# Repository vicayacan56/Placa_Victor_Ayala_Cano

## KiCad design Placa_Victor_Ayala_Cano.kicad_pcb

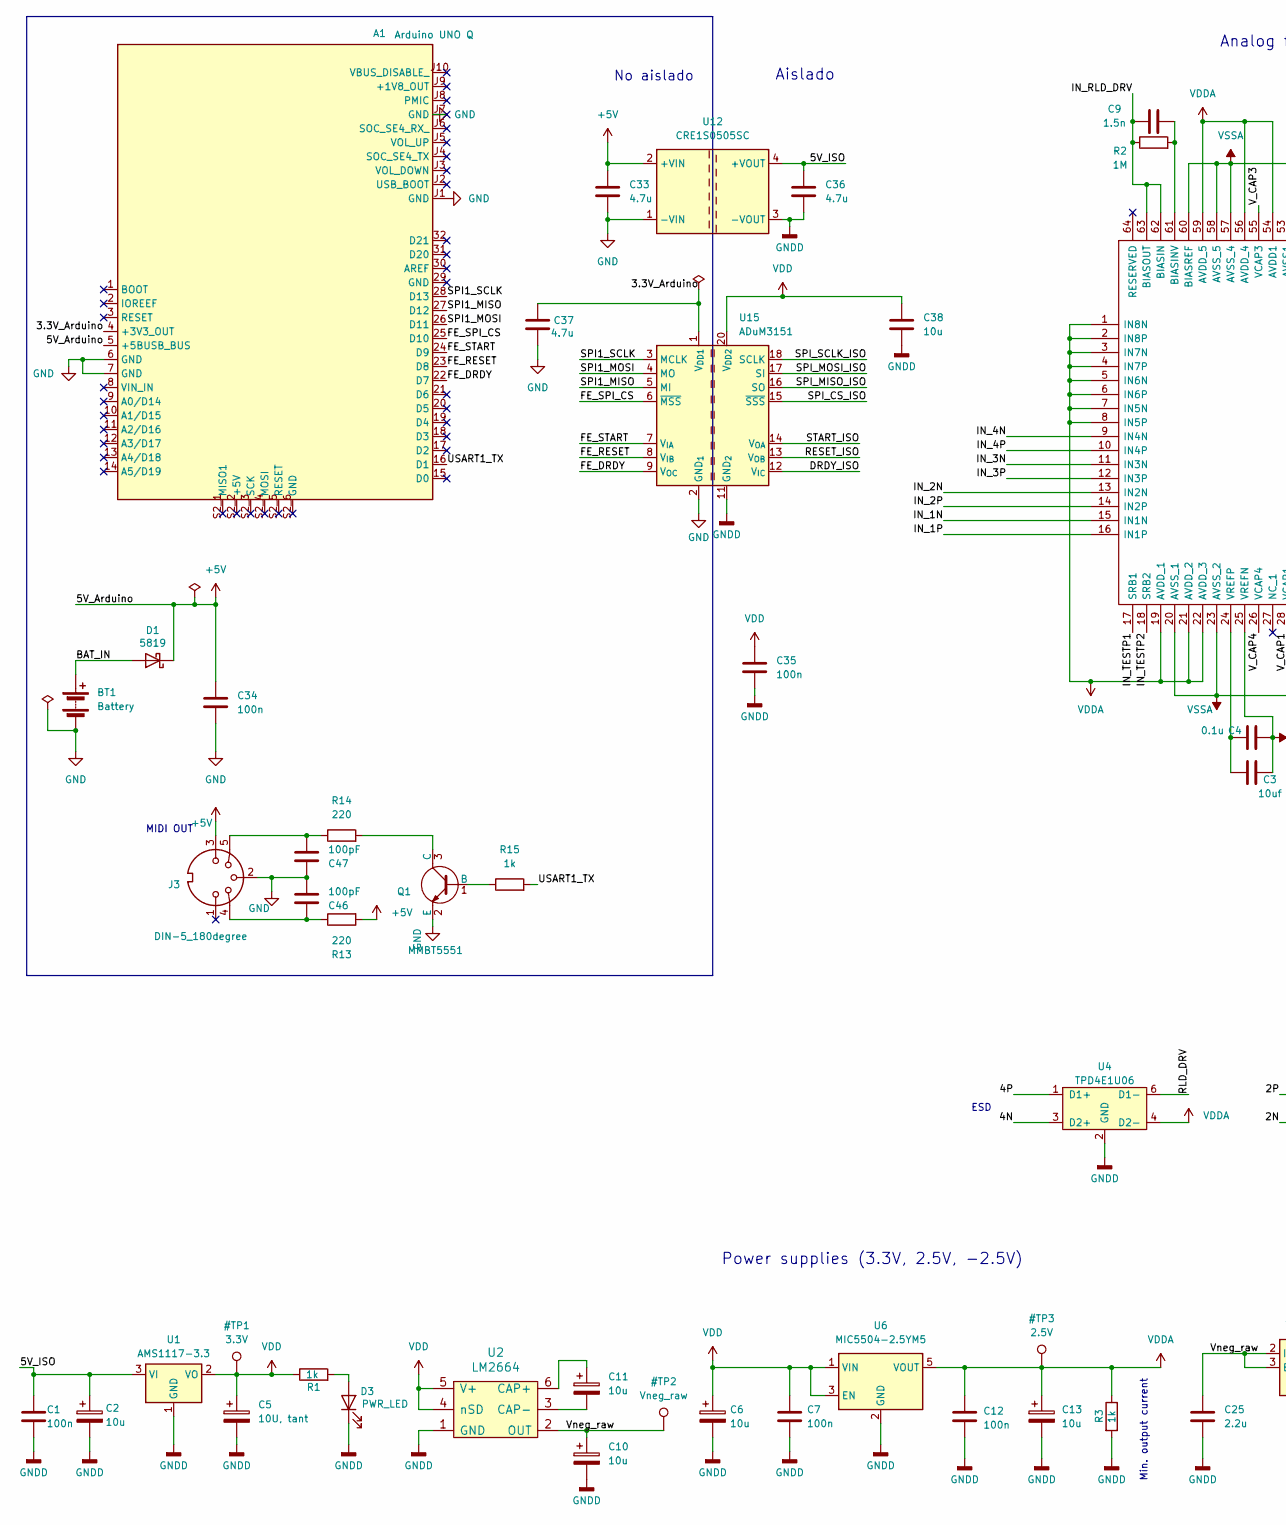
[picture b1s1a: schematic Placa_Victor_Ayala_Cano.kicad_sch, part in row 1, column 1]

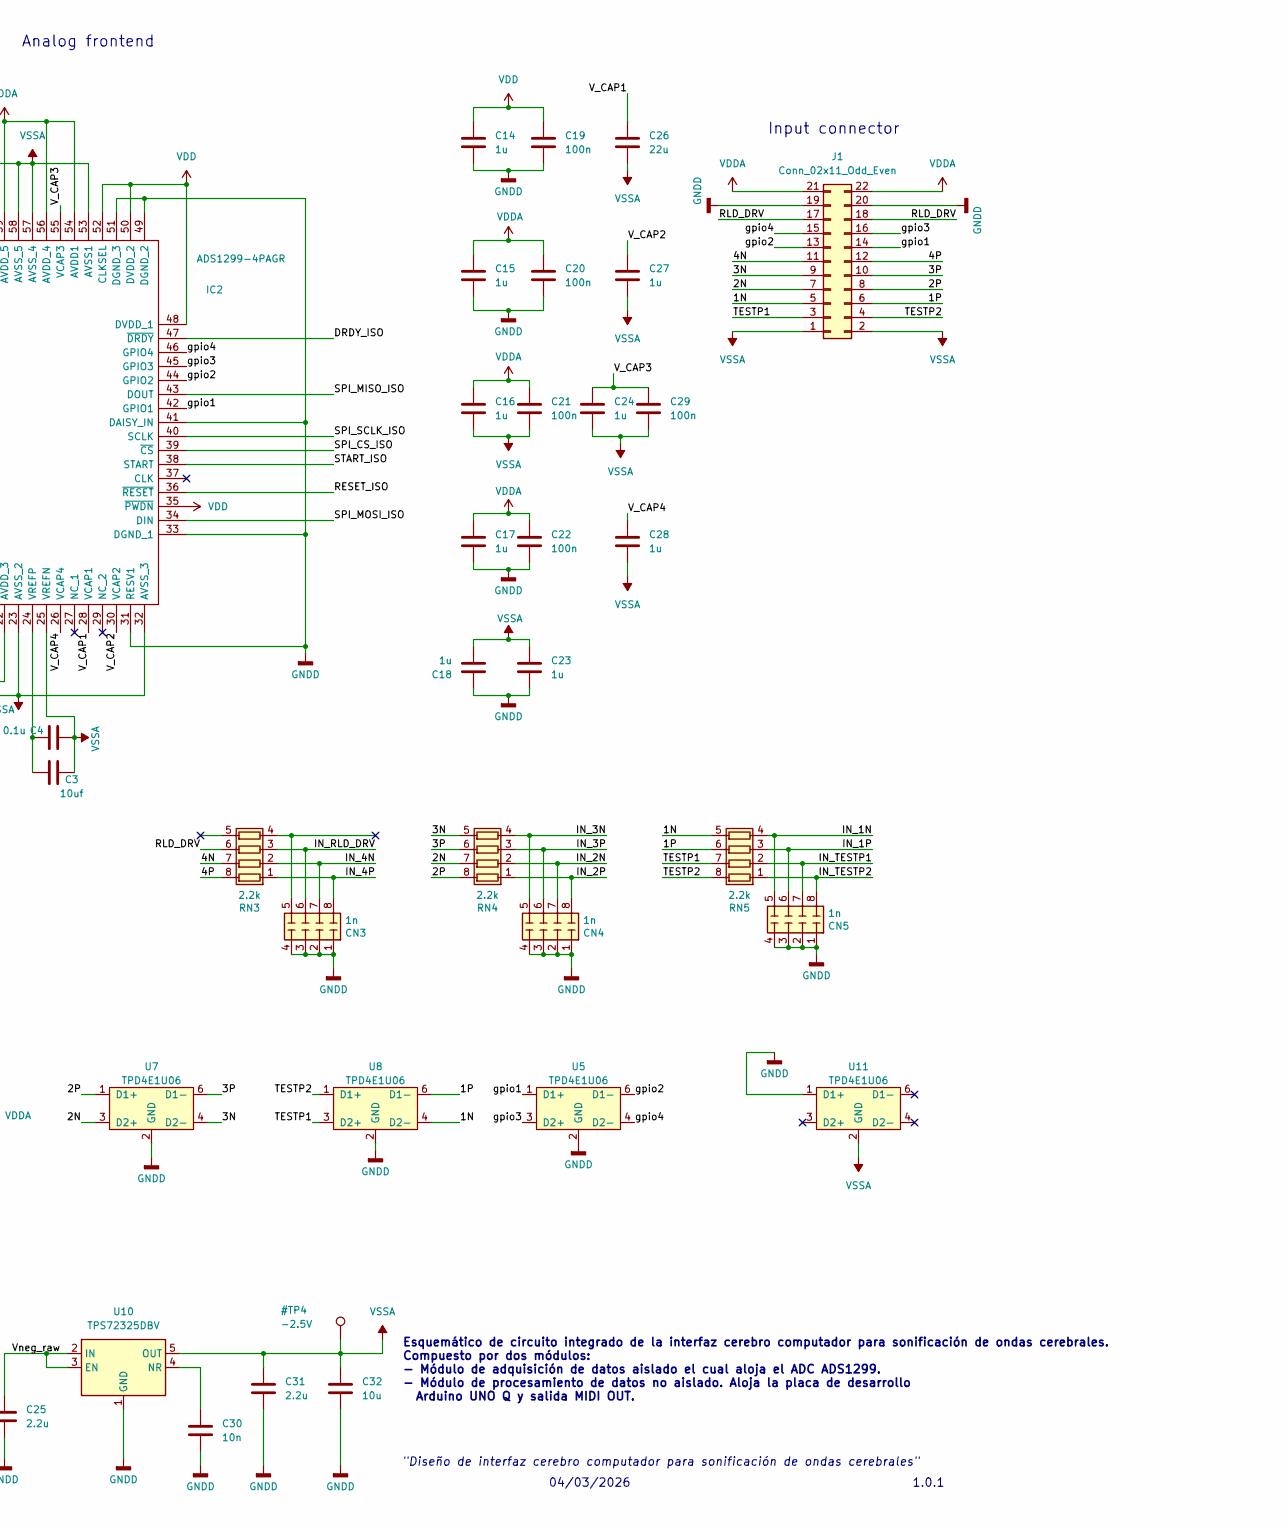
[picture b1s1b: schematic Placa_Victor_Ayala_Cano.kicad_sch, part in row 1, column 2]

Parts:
A1: Arduino UNO Q; Arduino_UNO_R3
BT1: Battery; PinHeader_1x02_P2.54mm_Vertical
C1, C7, C12, C19, C20, C21, C22, C29, C34, C35: 100n; C_0805_2012Metric_Pad1.18x1.45mm_HandSolder
C2, C6, C10, C11, C13, C32, C38: 10u; C_0805_2012Metric_Pad1.18x1.45mm_HandSolder
C3: 10uf; C_0805_2012Metric_Pad1.18x1.45mm_HandSolder
C4: 0.1u; C_0805_2012Metric_Pad1.18x1.45mm_HandSolder
C5: 10U, tant; C_0805_2012Metric_Pad1.18x1.45mm_HandSolder
C9: 1.5n; C_0805_2012Metric_Pad1.18x1.45mm_HandSolder
C14, C15, C16, C17, C18, C23, C24, C27, C28: 1u; C_0805_2012Metric_Pad1.18x1.45mm_HandSolder
C25, C31: 2.2u; C_0805_2012Metric_Pad1.18x1.45mm_HandSolder
C26: 22u; C_0805_2012Metric_Pad1.18x1.45mm_HandSolder
C30: 10n; C_0805_2012Metric_Pad1.18x1.45mm_HandSolder
C33, C36, C37: 4.7u; C_0805_2012Metric_Pad1.18x1.45mm_HandSolder
C46, C47: 100pF; C_0805_2012Metric_Pad1.18x1.45mm_HandSolder
CN3, CN4, CN5: 1n; R_Array_Convex_4x0603; LCSC C507409
D1: 5819; D_SOD-123; LCSC C82544
D3: PWR_LED; LED_0805_2012Metric
IC2: ADS1299-4PAGR; TQFP-64_10x10mm_P0.5mm; Mouser Part Number 595-ADS1299-4PAGR
J1: Conn_02x11_Odd_Even; PinHeader_2x11_P2.54mm_Vertical
J3: DIN-5_180degree; 57PC5FS; Manufacturer_Part_Number 57PC5FS
Q1: MMBT5551; SOT-23; Manufacturer_Part_Number MMBT5551
R1, R3, R15: 1k; R_0805_2012Metric
R2: 1M; R_0805_2012Metric
R13, R14: 220; R_0805_2012Metric
RN3, RN4, RN5: 2.2k; R_Array_Convex_4x0603; LCSC C12001
U1: AMS1117-3.3; SOT-223-3_TabPin2; Manufacturer_Part_Number AMS1117-3.3
U2: LM2664; SOT-23-6; Manufacturer_Part_Number LM2664; LCSC C108573
U4, U5, U7, U8, U11: TPD4E1U06; SOT-23-6; Manufacturer_Part_Number TPD4E1U06; LCSC C124691
U6: MIC5504-2.5YM5; SOT-23-5; Manufacturer_Part_Number MIC5504-2.5YM5
U10: TPS72325DBV; SOT-23-5; Manufacturer_Part_Number TPS72325DBV
U12: CRE1S0505SC; Converter_DCDC_Murata_CRE1xxxxxxSC_THT; Manufacturer_Part_Number CRE1S0505SC
U15: ADuM3151; SSOP-20_5.3x7.2mm_P0.65mm; Manufacturer_Part_Number ADuM3151

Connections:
+5V: A1.5 (+5BUSB_BUS), C33.1, C34.1, D1.1 (K), J3.3, R13.2, U12.2 (+VIN)
/1N: J1.5, RN5.5 (R4.2), U8.4 (D2-)
/1P: J1.6, RN5.6 (R3.2), U8.6 (D1-)
/2N: J1.7, RN4.7 (R2.2), U7.3 (D2+)
/2P: J1.8, RN4.8 (R1.2), U7.1 (D1+)
/3.3V_Arduino: A1.4 (+3V3_OUT), C37.1, U15.1 (V_{DD1})
/3N: J1.9, RN4.5 (R4.2), U7.4 (D2-)
/3P: J1.10, RN4.6 (R3.2), U7.6 (D1-)
/4N: J1.11, RN3.7 (R2.2), U4.3 (D2+)
/4P: J1.12, RN3.8 (R1.2), U4.1 (D1+)
/5V_ISO: C1.1, C2.1, C36.1, U1.3 (VI), U12.4 (+VOUT)
/BAT_IN: BT1.1 (+), D1.2 (A)
/DRDY_ISO: IC2.47 (~DRDY), U15.12 (V_{IC})
/FE_DRDY: A1.22 (D7), U15.9 (V_{OC})
/FE_RESET: A1.23 (D8), U15.8 (V_{IB})
/FE_SPI_CS: A1.25 (D10), U15.6 (~MSS)
/FE_START: A1.24 (D9), U15.7 (V_{IA})
/IN_1N: CN5.5 (R4.2), IC2.15 (IN1N), RN5.4 (R4.1)
/IN_1P: CN5.6 (R3.2), IC2.16 (IN1P), RN5.3 (R3.1)
/IN_2N: CN4.7 (R2.2), IC2.13 (IN2N), RN4.2 (R2.1)
/IN_2P: CN4.8 (R1.2), IC2.14 (IN2P), RN4.1 (R1.1)
/IN_3N: CN4.5 (R4.2), IC2.11 (IN3N), RN4.4 (R4.1)
/IN_3P: CN4.6 (R3.2), IC2.12 (IN3P), RN4.3 (R3.1)
/IN_4N: CN3.7 (R2.2), IC2.9 (IN4N), RN3.2 (R2.1)
/IN_4P: CN3.8 (R1.2), IC2.10 (IN4P), RN3.1 (R1.1)
/IN_RLD_DRV: C9.1, CN3.6 (R3.2), IC2.62 (BIASIN), IC2.63 (BIASOUT), R2.1, RN3.3 (R3.1)
/IN_TESTP1: CN5.7 (R2.2), IC2.17 (SRB1), RN5.2 (R2.1)
/IN_TESTP2: CN5.8 (R1.2), IC2.18 (SRB2), RN5.1 (R1.1)
/RESET_ISO: IC2.36 (~RESET), U15.13 (V_{OB})
/RLD_DRV: J1.17, J1.18, RN3.6 (R3.2), U4.6 (D1-)
/SPI1_MISO: A1.27 (D12), U15.5 (MI)
/SPI1_MOSI: A1.26 (D11), U15.4 (MO)
/SPI1_SCLK: A1.28 (D13), U15.3 (MCLK)
/SPI_CS_ISO: IC2.39 (~CS), U15.15 (~SSS)
/SPI_MISO_ISO: IC2.43 (DOUT), U15.16 (SO)
/SPI_MOSI_ISO: IC2.34 (DIN), U15.17 (SI)
/SPI_SCLK_ISO: IC2.40 (SCLK), U15.18 (SCLK)
/START_ISO: IC2.38 (START), U15.14 (V_{OA})
/TESTP1: J1.3, RN5.7 (R2.2), U8.3 (D2+)
/TESTP2: J1.4, RN5.8 (R1.2), U8.1 (D1+)
/USART1_TX: A1.16 (D1), R15.2
/V_CAP1: C26.1, IC2.28 (VCAP1)
/V_CAP2: C27.2, IC2.30 (VCAP2)
/V_CAP3: C24.1, C29.1, IC2.55 (VCAP3)
/V_CAP4: C28.1, IC2.26 (VCAP4)
/Vneg_raw: C10.1, C25.1, U2.2 (OUT), U10.2 (IN), U10.3 (EN)
/gpio1: IC2.42 (GPIO1), J1.14, U5.1 (D1+)
/gpio2: IC2.44 (GPIO2), J1.13, U5.6 (D1-)
/gpio3: IC2.45 (GPIO3), J1.16, U5.3 (D2+)
/gpio4: IC2.46 (GPIO4), J1.15, U5.4 (D2-)
GND: A1.6 (GND), A1.7 (GND), A1.J1 (GND), A1.J7 (GND), BT1.2 (-), C33.2, C34.2, C37.2, C46.1, C47.2, J3.2, Q1.2 (E), U12.1 (-VIN), U15.2 (GND_{1}), U15.10 (GND_{1})
GNDD: C1.2, C2.2, C5.2, C6.2, C7.2, C10.2, C12.2, C13.2, C14.1, C15.2, C17.2, C18.1, C19.2, C20.2, C22.2, C23.2, C25.2, C30.2, C31.2, C32.2, C35.2, C36.2, C38.2, CN3.1 (R1.1), CN3.2 (R2.1), CN3.3 (R3.1), CN3.4 (R4.1), CN4.1 (R1.1), CN4.2 (R2.1), CN4.3 (R3.1), CN4.4 (R4.1), CN5.1 (R1.1), CN5.2 (R2.1), CN5.3 (R3.1), CN5.4 (R4.1), D3.1 (K), IC2.31 (RESV1), IC2.33 (DGND_1), IC2.41 (DAISY_IN), IC2.49 (DGND_2), IC2.51 (DGND_3), J1.19, J1.20, R3.2, U1.1 (GND), U2.1 (GND), U4.2 (GND), U5.2 (GND), U6.2 (GND), U7.2 (GND), U8.2 (GND), U10.1 (GND), U11.1 (D1+), U12.3 (-VOUT), U15.11 (GND_{2}), U15.19 (GND_{2})
unnamed: C46.2, J3.4, R13.1
unnamed: C47.1, J3.5, R14.1
unnamed: D3.2 (A), R1.2
unnamed: C9.2, IC2.61 (BIASINV), R2.2
unnamed: C3.1, C4.1, IC2.24 (VREFP)
unnamed: Q1.1 (B), R15.1
unnamed: Q1.3 (C), R14.2
unnamed: C11.1, U2.6 (CAP+)
unnamed: C11.2, U2.3 (CAP-)
unnamed: C30.1, U10.4 (NR)
VDD: C5.1, C6.1, C7.1, C14.2, C19.1, C35.1, C38.1, IC2.35 (~PWDN), IC2.48 (DVDD_1), IC2.50 (DVDD_2), IC2.52 (CLKSEL), R1.1, U1.2 (VO), U2.4 (nSD), U2.5 (V+), U6.1 (VIN), U6.3 (EN), U15.20 (V_{DD2})
VDDA: C12.1, C13.1, C15.1, C16.1, C17.1, C20.1, C21.1, C22.1, IC2.1 (IN8N), IC2.2 (IN8P), IC2.3 (IN7N), IC2.4 (IN7P), IC2.5 (IN6N), IC2.6 (IN6P), IC2.7 (IN5N), IC2.8 (IN5P), IC2.19 (AVDD_1), IC2.21 (AVDD_2), IC2.22 (AVDD_3), IC2.54 (AVDD1), IC2.56 (AVDD_4), IC2.59 (AVDD_5), J1.21, J1.22, R3.1, U4.4 (D2-), U6.5 (VOUT)
VSSA: C3.2, C4.2, C16.2, C18.2, C21.2, C23.1, C24.2, C26.2, C27.1, C28.2, C29.2, C31.1, C32.1, IC2.20 (AVSS_1), IC2.23 (AVSS_2), IC2.25 (VREFN), IC2.32 (AVSS_3), IC2.53 (AVSS1), IC2.57 (AVSS_4), IC2.58 (AVSS_5), IC2.60 (BIASREF), J1.1, J1.2, U10.5 (OUT), U11.2 (GND)

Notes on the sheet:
Analog frontend
Min. output current
Power supplies (3.3V, 2.5V, -2.5V)
No aislado
04/03/2026
Input connector
Esquemático de circuito integrado de la interfaz cerebro computador para sonificación de ondas cerebrales. Compuesto por dos módulos: - Módulo de adquisición de datos aislado el cual aloja el ADC ADS1299. - Módulo de procesamiento de datos no aislado. Aloja la placa de desarrollo Arduino UNO Q y sa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
1.0.1
"Diseño de interfaz cerebro computador para sonificación de ondas cerebrales"
MIDI OUT
Aislado
ESD

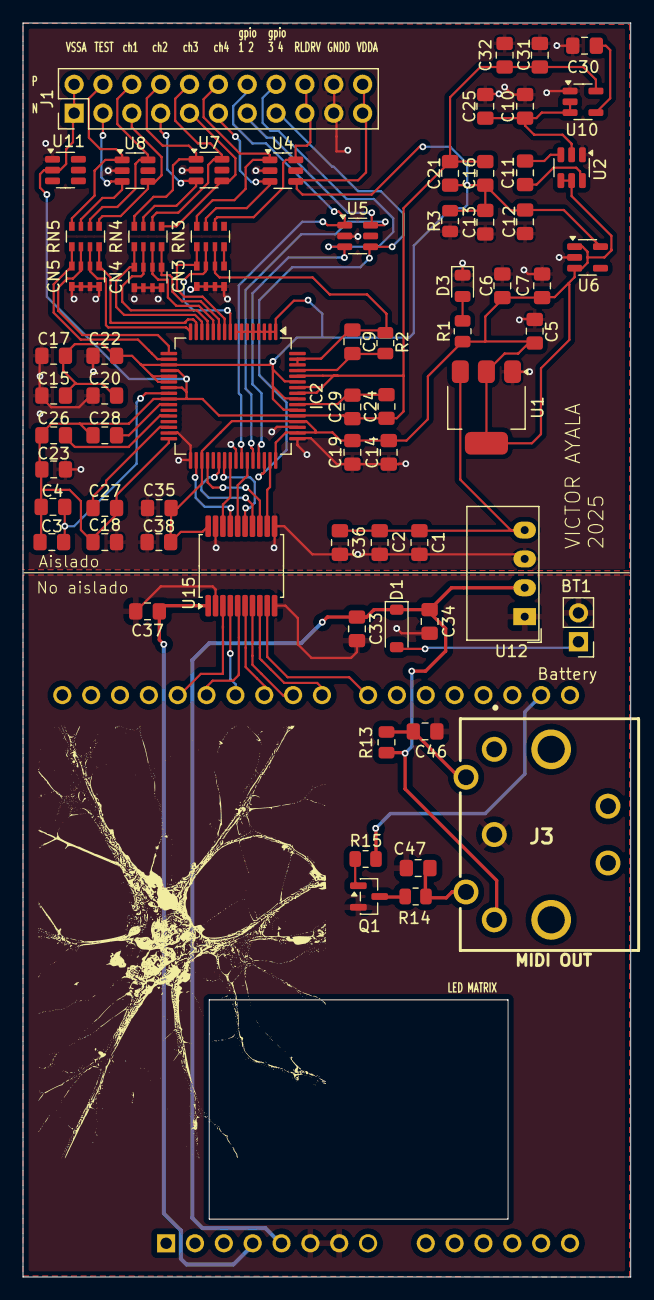
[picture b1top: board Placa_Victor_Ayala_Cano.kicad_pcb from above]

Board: 2 copper layers, 53.5 x 110.4 mm, 70 parts (1 on the bottom side), 65 nets.

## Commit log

2026-03-18 Initial commit - KiCad PCB project
2026-03-18 Update: rutas relativas, modelos 3D y librerías locales
